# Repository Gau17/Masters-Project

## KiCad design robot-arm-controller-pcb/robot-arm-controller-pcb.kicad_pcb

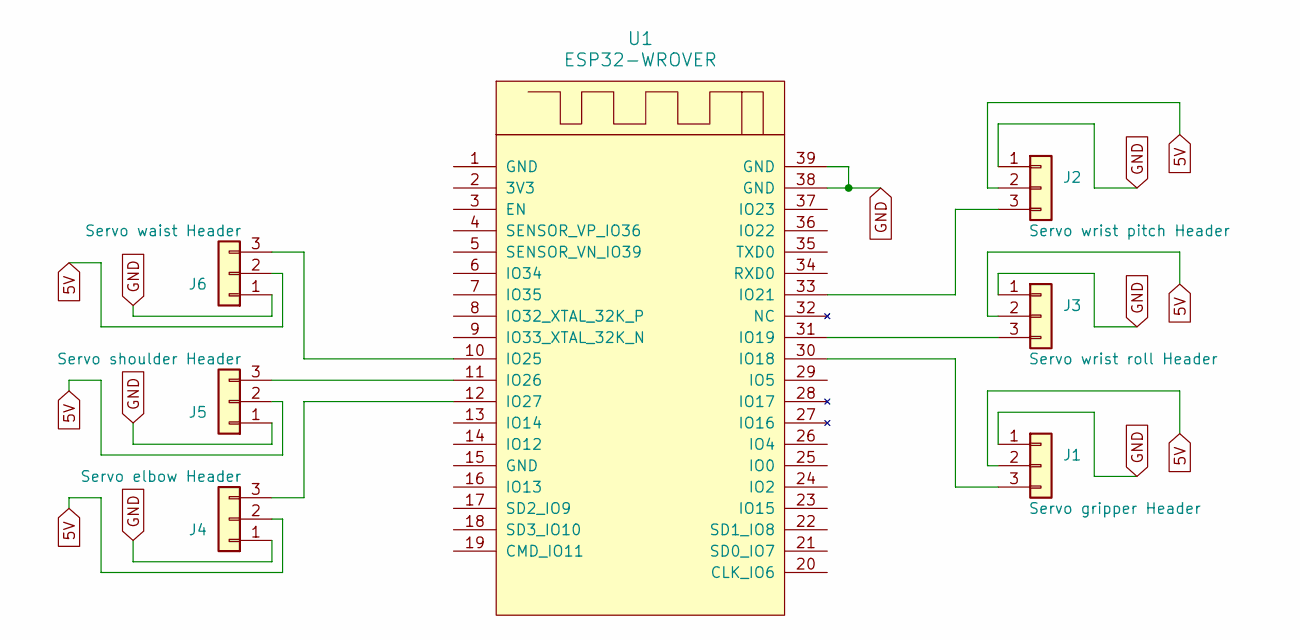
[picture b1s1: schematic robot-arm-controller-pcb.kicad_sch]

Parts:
J1: Servo gripper Header; PinHeader_1x03_P2.54mm_Vertical
J2: Servo wrist pitch Header; PinHeader_1x03_P2.54mm_Vertical
J3: Servo wrist roll Header; PinHeader_1x03_P2.54mm_Vertical
J4: Servo elbow Header; PinHeader_1x03_P2.54mm_Vertical
J5: Servo shoulder Header; PinHeader_1x03_P2.54mm_Vertical
J6: Servo waist Header; PinHeader_1x03_P2.54mm_Vertical
U1: ESP32-WROVER

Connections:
5V: J1.2, J2.2, J3.2, J4.2, J5.2, J6.2
GND: J1.1, J2.1, J3.1, J4.1, J5.1, J6.1, U1.38 (GND), U1.39 (GND)
unnamed: J1.3, U1.30 (IO18)
unnamed: J2.3, U1.33 (IO21)
unnamed: J3.3, U1.31 (IO19)
unnamed: J4.3, U1.12 (IO27)
unnamed: J5.3, U1.11 (IO26)
unnamed: J6.3, U1.10 (IO25)

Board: 2 copper layers, 7 parts (0 on the bottom side), 8 nets, no tracks yet.

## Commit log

2025-05-17 Added initial repo structure
2025-05-25 added servo control, WIP
2025-05-25 unit testing setup
2025-05-28 Added servo unit tests
2025-05-31 Added wifi comms initial code, WIP
2025-06-04 updated code to include all 6 servo control, tested working
2025-06-04 added initial pcb design schematic - WIP
2025-06-10 added pose structure and tests
2025-06-20 added coap, basic setup
2025-07-04 added coap post request example
2025-07-04 added rpi aiocoap server
2025-08-01 added esp32 coap server
2025-08-01 added cbor encoding for servo cmd
2025-08-15 final experiment changes
